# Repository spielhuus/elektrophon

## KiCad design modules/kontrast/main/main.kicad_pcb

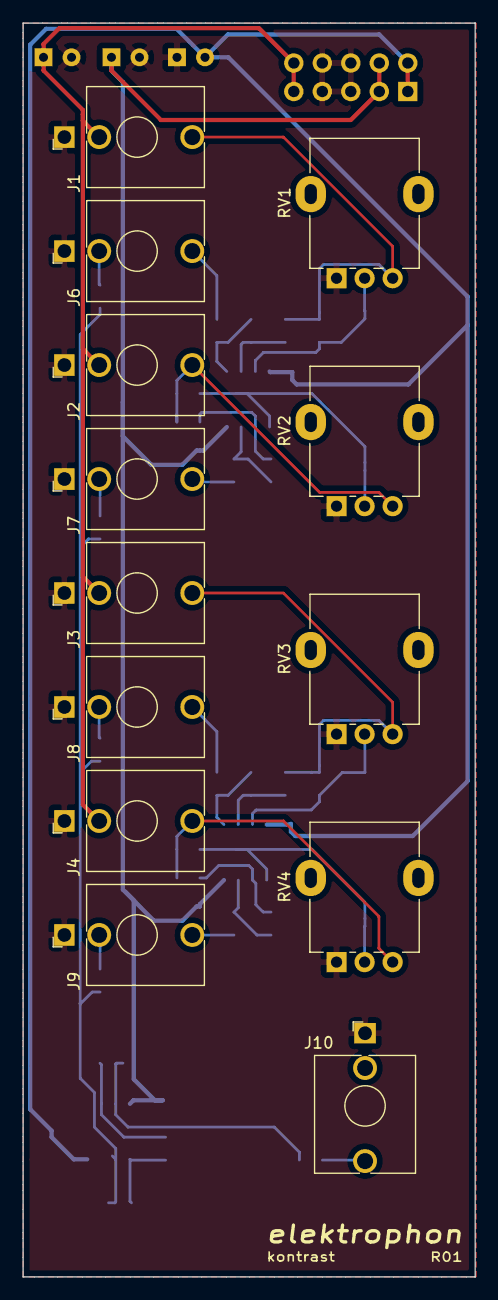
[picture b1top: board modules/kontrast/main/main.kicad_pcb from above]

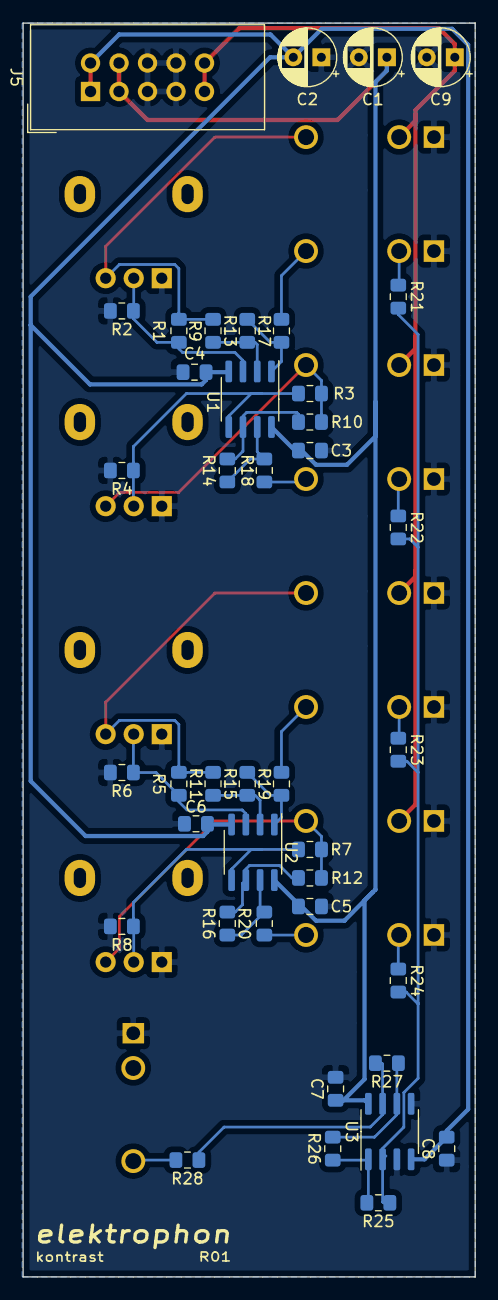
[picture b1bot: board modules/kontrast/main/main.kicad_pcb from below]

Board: 2 copper layers, 40.3 x 111.8 mm, 54 parts (41 on the bottom side), 33 nets.

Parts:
C1, C2, C9: 10u; CP_Radial_D5.0mm_P2.50mm
C3, C4, C5, C6, C7, C8: 0.1u; C_0805_2012Metric_Pad1.15x1.40mm_HandSolder
J1, J2, J3, J4: IN; Jack_3.5mm_WQP-PJ398SM_Vertical
J5: IDC Header; IDC-Header_2x05_P2.54mm_Vertical
J6, J7, J8, J9, J10: OUT; Jack_3.5mm_WQP-PJ398SM_Vertical
R1, R2, R3, R4, R5, R6, R7, R8: 47k; R_0805_2012Metric_Pad1.15x1.40mm_HandSolder
R9, R10, R11, R12, R13, R14, R15, R16, R21, R22, R23, R24, R25, R26, R27: 100k; R_0805_2012Metric_Pad1.15x1.40mm_HandSolder
R17, R18, R19, R20, R28: 1k; R_0805_2012Metric_Pad1.15x1.40mm_HandSolder
RV1, RV2, RV3, RV4: 100k; Potentiometer_Alpha_RD901F-40-00D_Single_Vertical
U1, U2, U3: OPA2134; SOIC-8_3.9x4.9mm_P1.27mm

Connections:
+5V: C9.1, J1.TN, J2.TN, J3.TN, J4.TN, J5.9, J5.10
+15V: C1.1, C3.1, C5.1, C7.1, J5.3, J5.4, U1.8, U2.8, U3.8
-15V: C2.2, C4.2, C6.2, C8.2, J5.1, J5.2, U1.4, U2.4, U3.4
/MIX_1: J6.TN, R21.1
/MIX_2: J7.TN, R22.1
/MIX_3: J8.TN, R23.1
/MIX_4: J9.TN, R24.1
GND: C1.2, C2.1, C3.2, C4.1, C5.2, C6.1, C7.2, C8.1, C9.2, J1.S, J2.S, J3.S, J4.S, J5.5, J5.6, J5.7, J5.8, J6.S, J7.S, J8.S, J9.S, J10.S, R2.2, R4.2, R6.2, R8.2, RV1.1, RV2.1, RV3.1, RV4.1, U3.3, U3.5
unnamed: J1.T, R1.1, R9.2, RV1.3
unnamed: J2.T, R3.1, R10.2, RV2.3
unnamed: J3.T, R5.1, R11.2, RV3.3
unnamed: J4.T, R7.1, R12.2, RV4.3
unnamed: J6.T, R17.2
unnamed: J7.T, R18.2
unnamed: J8.T, R19.2
unnamed: J9.T, R20.2
unnamed: J10.T, R28.2
unnamed: R1.2, R2.1, RV1.2, U1.3
unnamed: R3.2, R4.1, RV2.2, U1.5
unnamed: R5.2, R6.1, RV3.2, U2.3
unnamed: R7.2, R8.1, RV4.2, U2.5
unnamed: R10.1, R14.2, U1.6
unnamed: R11.1, R15.2, U2.2
unnamed: R12.1, R16.2, U2.6
unnamed: R13.1, R17.1, U1.1
unnamed: R9.1, R13.2, U1.2
unnamed: R14.1, R18.1, U1.7
unnamed: R15.1, R19.1, U2.1
unnamed: R16.1, R20.1, U2.7
unnamed: R21.2, R22.2, R23.2, R24.2, R25.1, U3.2
unnamed: R25.2, R26.1, U3.1
unnamed: R26.2, R27.1, U3.6
unnamed: R27.2, R28.1, U3.7

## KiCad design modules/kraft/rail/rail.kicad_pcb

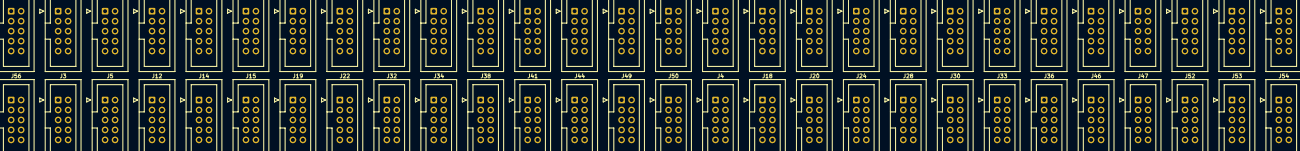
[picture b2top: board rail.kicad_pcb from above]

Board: 2 copper layers, 60 parts (0 on the bottom side), 4 nets, no tracks yet.

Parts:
H1, H2, H3, H4: MountingHole; MountingHole_2.2mm_M2
J1, J2, J3, J4, J5, J6, J7, J8, J9, J10, J11, J12, J13, J14, J15, J16, J17, J18, J19, J20, J21, J22, J23, J24, J25, J26, J27, J28, J29, J30, J31, J32, J33, J34, J35, J36, J37, J38, J39, J40, J41, J42, J43, J44, J45, J46, J47, J48, J49, J50, J51, J52, J53, J54, J55, J56: IDC Header; IDC-Header_2x05_P2.54mm_Vertical

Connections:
+5V: J1.9, J1.10, J2.9, J2.10, J3.9, J3.10, J4.9, J4.10, J5.9, J5.10, J6.9, J6.10, J7.9, J7.10, J8.9, J8.10, J9.9, J9.10, J10.9, J10.10, J11.9, J11.10, J12.9, J12.10, J13.9, J13.10, J14.9, J14.10, J15.9, J15.10, J16.9, J16.10, J17.9, J17.10, J18.9, J18.10, J19.9, J19.10, J20.9, J20.10, J21.9, J21.10, J22.9, J22.10, J23.9, J23.10, J24.9, J24.10, J25.9, J25.10, J26.9, J26.10, J27.9, J27.10, J28.9, J28.10, J29.9, J29.10, J30.9, J30.10, J31.9, J31.10, J32.9, J32.10, J33.9, J33.10, J34.9, J34.10, J35.9, J35.10, J36.9, J36.10, J37.9, J37.10, J38.9, J38.10, J39.9, J39.10, J40.9, J40.10, J41.9, J41.10, J42.9, J42.10, J43.9, J43.10, J44.9, J44.10, J45.9, J45.10, J46.9, J46.10, J47.9, J47.10, J48.9, J48.10, J49.9, J49.10, J50.9, J50.10, J51.9, J51.10, J52.9, J52.10, J53.9, J53.10, J54.9, J54.10, J55.9, J55.10, J56.9, J56.10
+15V: J1.3, J1.4, J2.3, J2.4, J3.3, J3.4, J4.3, J4.4, J5.3, J5.4, J6.3, J6.4, J7.3, J7.4, J8.3, J8.4, J9.3, J9.4, J10.3, J10.4, J11.3, J11.4, J12.3, J12.4, J13.3, J13.4, J14.3, J14.4, J15.3, J15.4, J16.3, J16.4, J17.3, J17.4, J18.3, J18.4, J19.3, J19.4, J20.3, J20.4, J21.3, J21.4, J22.3, J22.4, J23.3, J23.4, J24.3, J24.4, J25.3, J25.4, J26.3, J26.4, J27.3, J27.4, J28.3, J28.4, J29.3, J29.4, J30.3, J30.4, J31.3, J31.4, J32.3, J32.4, J33.3, J33.4, J34.3, J34.4, J35.3, J35.4, J36.3, J36.4, J37.3, J37.4, J38.3, J38.4, J39.3, J39.4, J40.3, J40.4, J41.3, J41.4, J42.3, J42.4, J43.3, J43.4, J44.3, J44.4, J45.3, J45.4, J46.3, J46.4, J47.3, J47.4, J48.3, J48.4, J49.3, J49.4, J50.3, J50.4, J51.3, J51.4, J52.3, J52.4, J53.3, J53.4, J54.3, J54.4, J55.3, J55.4, J56.3, J56.4
-15V: J1.1, J1.2, J2.1, J2.2, J3.1, J3.2, J4.1, J4.2, J5.1, J5.2, J6.1, J6.2, J7.1, J7.2, J8.1, J8.2, J9.1, J9.2, J10.1, J10.2, J11.1, J11.2, J12.1, J12.2, J13.1, J13.2, J14.1, J14.2, J15.1, J15.2, J16.1, J16.2, J17.1, J17.2, J18.1, J18.2, J19.1, J19.2, J20.1, J20.2, J21.1, J21.2, J22.1, J22.2, J23.1, J23.2, J24.1, J24.2, J25.1, J25.2, J26.1, J26.2, J27.1, J27.2, J28.1, J28.2, J29.1, J29.2, J30.1, J30.2, J31.1, J31.2, J32.1, J32.2, J33.1, J33.2, J34.1, J34.2, J35.1, J35.2, J36.1, J36.2, J37.1, J37.2, J38.1, J38.2, J39.1, J39.2, J40.1, J40.2, J41.1, J41.2, J42.1, J42.2, J43.1, J43.2, J44.1, J44.2, J45.1, J45.2, J46.1, J46.2, J47.1, J47.2, J48.1, J48.2, J49.1, J49.2, J50.1, J50.2, J51.1, J51.2, J52.1, J52.2, J53.1, J53.2, J54.1, J54.2, J55.1, J55.2, J56.1, J56.2
GND: J1.5, J1.6, J1.7, J1.8, J2.5, J2.6, J2.7, J2.8, J3.5, J3.6, J3.7, J3.8, J4.5, J4.6, J4.7, J4.8, J5.5, J5.6, J5.7, J5.8, J6.5, J6.6, J6.7, J6.8, J7.5, J7.6, J7.7, J7.8, J8.5, J8.6, J8.7, J8.8, J9.5, J9.6, J9.7, J9.8, J10.5, J10.6, J10.7, J10.8, J11.5, J11.6, J11.7, J11.8, J12.5, J12.6, J12.7, J12.8, J13.5, J13.6, J13.7, J13.8, J14.5, J14.6, J14.7, J14.8, J15.5, J15.6, J15.7, J15.8, J16.5, J16.6, J16.7, J16.8, J17.5, J17.6, J17.7, J17.8, J18.5, J18.6, J18.7, J18.8, J19.5, J19.6, J19.7, J19.8, J20.5, J20.6, J20.7, J20.8, J21.5, J21.6, J21.7, J21.8, J22.5, J22.6, J22.7, J22.8, J23.5, J23.6, J23.7, J23.8, J24.5, J24.6, J24.7, J24.8, J25.5, J25.6, J25.7, J25.8, J26.5, J26.6, J26.7, J26.8, J27.5, J27.6, J27.7, J27.8, J28.5, J28.6, J28.7, J28.8, J29.5, J29.6, J29.7, J29.8, J30.5, J30.6, J30.7, J30.8, J31.5, J31.6, J31.7, J31.8, J32.5, J32.6, J32.7, J32.8, J33.5, J33.6, J33.7, J33.8, J34.5, J34.6, J34.7, J34.8, J35.5, J35.6, J35.7, J35.8, J36.5, J36.6, J36.7, J36.8, J37.5, J37.6, J37.7, J37.8, J38.5, J38.6, J38.7, J38.8, J39.5, J39.6, J39.7, J39.8, J40.5, J40.6, J40.7, J40.8, J41.5, J41.6, J41.7, J41.8, J42.5, J42.6, J42.7, J42.8, J43.5, J43.6, J43.7, J43.8, J44.5, J44.6, J44.7, J44.8, J45.5, J45.6, J45.7, J45.8, J46.5, J46.6, J46.7, J46.8, J47.5, J47.6, J47.7, J47.8, J48.5, J48.6, J48.7, J48.8, J49.5, J49.6, J49.7, J49.8, J50.5, J50.6, J50.7, J50.8, J51.5, J51.6, J51.7, J51.8, J52.5, J52.6, J52.7, J52.8, J53.5, J53.6, J53.7, J53.8, J54.5, J54.6, J54.7, J54.8, J55.5, J55.6, J55.7, J55.8, J56.5, J56.6, J56.7, J56.8

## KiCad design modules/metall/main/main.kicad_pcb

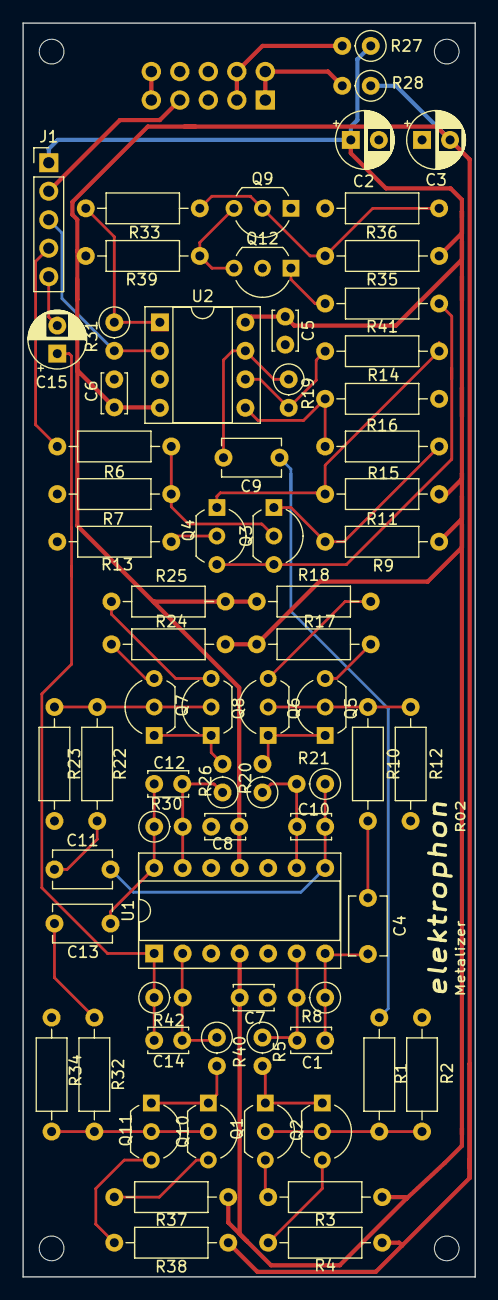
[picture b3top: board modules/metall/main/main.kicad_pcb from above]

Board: 2 copper layers, 40.3 x 111.8 mm, 76 parts (1 on the bottom side), 49 nets.

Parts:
C1, C10, C12, C14: 27p; C_Disc_D3.4mm_W2.1mm_P2.50mm
C2, C3, C15: 10u; CP_Radial_D5.0mm_P2.50mm
C4, C9, C11, C13: 680n; C_Disc_D5.1mm_W3.2mm_P5.00mm
C5, C6, C7, C8: 0.1u; C_Disc_D3.4mm_W2.1mm_P2.50mm
H1, H2, H3, H4: MountingHole; MountingHole_2.2mm_M2
J1: Conn_01x05_Female; PinHeader_1x05_P2.54mm_Vertical
J2: POWER; IDC-Header_2x05_P2.54mm_Vertical
Q1, Q5, Q7, Q10: BC559; TO-92_Inline_Wide
Q2, Q6, Q8, Q11: BC549; TO-92_Inline_Wide
Q3, Q4, Q9, Q12: BC547; TO-92_Inline_Wide
R1, R10, R22, R32: 27k; R_Axial_DIN0207_L6.3mm_D2.5mm_P10.16mm_Horizontal
R2, R12, R23, R34: 68k; R_Axial_DIN0207_L6.3mm_D2.5mm_P10.16mm_Horizontal
R3, R4, R17, R18, R24, R25, R37, R38: 22k; R_Axial_DIN0207_L6.3mm_D2.5mm_P10.16mm_Horizontal
R5, R20, R26, R40: 10k; R_Axial_DIN0207_L6.3mm_D2.5mm_P2.54mm_Vertical
R6, R35: 120k; R_Axial_DIN0207_L6.3mm_D2.5mm_P10.16mm_Horizontal
R7: 820; R_Axial_DIN0207_L6.3mm_D2.5mm_P10.16mm_Horizontal
R8, R21, R30, R42: 120k; R_Axial_DIN0207_L6.3mm_D2.5mm_P2.54mm_Vertical
R9, R11, R14, R15: 15k; R_Axial_DIN0207_L6.3mm_D2.5mm_P10.16mm_Horizontal
R13: 1k; R_Axial_DIN0207_L6.3mm_D2.5mm_P10.16mm_Horizontal
R16: 150k; R_Axial_DIN0207_L6.3mm_D2.5mm_P10.16mm_Horizontal
R19, R31: 150k; R_Axial_DIN0207_L6.3mm_D2.5mm_P2.54mm_Vertical
R27, R28: 10; R_Axial_DIN0207_L6.3mm_D2.5mm_P2.54mm_Vertical
R33: 100k; R_Axial_DIN0207_L6.3mm_D2.5mm_P10.16mm_Horizontal
R36: 1k5; R_Axial_DIN0207_L6.3mm_D2.5mm_P10.16mm_Horizontal
R39: 18k; R_Axial_DIN0207_L6.3mm_D2.5mm_P10.16mm_Horizontal
R41: 10; R_Axial_DIN0207_L6.3mm_D2.5mm_P10.16mm_Horizontal
U1: TL074; DIP-14_W7.62mm_Socket
U2: TL072; DIP-8_W7.62mm_Socket

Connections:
+5V: J2.9, J2.10
+15V: C2.1, C5.1, C7.1, J1.1, R3.2, R9.2, R11.2, R17.2, R24.2, R27.1, R35.2, R37.2, U1.4, U2.8
-15V: C3.2, C6.2, C8.2, R4.1, R18.1, R25.1, R28.1, R38.1, R39.1, U1.11, U2.4
/CV1: J1.3, R31.2, U2.2
/CV2: Q3.3, Q4.3, R41.2
/IN: J1.4, R6.2
/INPUT: C9.1, R1.2
/OUT: C15.2, J1.5
GND: C2.2, C3.1, C5.2, C6.1, C7.2, C8.1, J1.2, J2.5, J2.6, J2.7, J2.8, Q9.1, Q12.2, R2.2, R7.1, R12.2, R13.1, R16.1, R23.2, R34.2, R36.1, U1.3, U1.5, U1.10, U1.12, U2.3
unnamed: C1.1, C4.2, R8.1, U1.7
unnamed: C1.2, R5.1, R8.2, U1.6
unnamed: C4.1, R10.2
unnamed: C9.2, R19.1, U2.7
unnamed: C10.1, C11.2, R21.1, U1.8
unnamed: C10.2, R20.1, R21.2, U1.9
unnamed: C11.1, R22.2
unnamed: C12.1, C13.2, R30.1, U1.14
unnamed: C12.2, R26.1, R30.2, U1.13
unnamed: C13.1, R32.2
unnamed: C14.1, C15.1, R42.1, U1.1
unnamed: C14.2, R40.1, R42.2, U1.2
unnamed: Q1.1, Q2.1, R5.2
unnamed: Q1.2, Q2.2, R1.1, R2.1
unnamed: Q1.3, R3.1
unnamed: Q2.3, R4.2
unnamed: Q3.1, R9.1, R15.2
unnamed: Q3.2, R6.1, R7.2
unnamed: Q4.1, R11.1, R14.2
unnamed: Q4.2, R13.2
unnamed: Q5.1, Q6.1, R20.2
unnamed: Q5.2, Q6.2, R10.1, R12.1
unnamed: Q5.3, R17.1
unnamed: Q6.3, R18.2
unnamed: Q7.1, Q8.1, R26.2
unnamed: Q7.2, Q8.2, R22.1, R23.1
unnamed: Q7.3, R24.1
unnamed: Q8.3, R25.2
unnamed: Q9.2, R33.1, R35.1, R36.2
unnamed: Q10.1, Q11.1, R40.2
unnamed: Q10.2, Q11.2, R32.1, R34.1
unnamed: Q10.3, R37.1
unnamed: Q11.3, R38.2
unnamed: Q12.1, R41.1
unnamed: Q9.3, Q12.3, R39.2
unnamed: R14.1, R19.2, U2.6
unnamed: R15.1, R16.2, U2.5
unnamed: R31.1, R33.2, U2.1
PWR_+15V: J2.3, J2.4, R27.2
PWR_-15V: J2.1, J2.2, R28.2

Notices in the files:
modules/kontrast/main/main.kicad_pcb:
License CC BY 4.0 - Attribution 4.0 International
